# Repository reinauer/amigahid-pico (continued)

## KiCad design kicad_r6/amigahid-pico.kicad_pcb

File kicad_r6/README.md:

# AmigaHID Pico r6 — prototype hardware

Open `amigahid-pico.kicad_pro` with KiCad 10.
The schematic and PCB in this directory are the r6 design, not fabrication-proven hardware.

## Implemented

- Pico **W** (RP2040, LCSC C7203003) fitted by default; also supports Pico **2 W**
  (RP2350) on the same footprint. Both modules provide Wi-Fi/Bluetooth. A bare RP2350 + RM2 design is
  deferred; it requires a separate MCU power/flash/clock/RF layout.
- Two **SN74CBTD3861DBQR** 10-channel bus switches replace all 17 BSS138 level
  shifters. Ten isolated 4 × 10 kΩ resistor arrays replace 34 individual
  pull-ups; unused resistor channels and switch channels are intentionally NC.
  These are the **CBTD** parts, powered from 5 V; CBTLV3861 is not a substitute.
- Two PCB-mounted **female DE9** connectors, numbered by actual DE9 pins rather
  than the old IDC/ribbon interleave. They connect to the Amiga's male ports.
- A **6-pin mini-DIN A4000 keyboard link**, for the user's straight-through
  PS/2-to-PS/2 cable and A4000-to-A3000 mini-DIN/DIN adapter. The signalling is
  Amiga keyboard protocol. This is not a PC PS/2 keyboard input.
- A four-pin female OLED socket, **3V3 / GND / SCL / SDA**, matching the supplied
  SH1106 module pin table. GPIO2 is SDA; GPIO3 is SCL.
- Four 3.2 mm carrier holes for M3 nylon standoffs on **30.50 × 28.60 mm** centres.
  The OLED outline is **35.50 × 33.70 mm**, from the supplied mechanical drawing.
- One USB-A host port. Full underside Pico W USB pads replace the old board
  crevice / half-via attachment. GPIO14/15 are exposed at J8 for a future PIO-USB
  experiment; the USB-A port currently uses the native USB controller.
- External 5 V input and a power-source selector, plus a 500 mA hold PTC on the
  USB host branch. An external powered USB hub provides multiple device ports.

Two additional case mounts, H5 at (2.70, 63.00) mm and H6 at (53.30, 22.50) mm,
use **2.2 mm holes for M2 nylon screws/standoffs**. Coordinates are measured from
the top-left board corner. Use hardware no wider than 4.4 mm at the PCB; M3
hardware crowds the Pico. H1–H4 remain the OLED mounts.

The carrier has a **14 × 9 mm antenna notch** from x=10 to 24 mm and y=59 to
68 mm, open to the bottom edge. This removes the carrier substrate beneath the
antenna, following the module footprint’s suggested board edge. Keep case metal
and mounting hardware out of that antenna space.

Board bounding outline: **70 × 68 mm**, two copper layers. The bounding rectangle is about 6.4% greater area
than the original outline's 61.772 × 72.443 mm bounding box. The level-shifting
section is smaller; the direct connectors and OLED mounting determine the
carrier size. Three onboard USB sockets and an onboard hub are not included.

## LCSC sourcing

`SOURCING.csv` records the selected manufacturer part numbers, datasheet links,
and footprint checks. The schematic
and PCB use only **LCSC Part #**, the field recognized by the Fabrication Toolkit
plugin. `production/bom.csv` uses the same **LCSC Part #** column. LCSC stock does not itself guarantee JLC assembly stock
or eligibility; check those when uploading the BOM.

All 32 electrical components have LCSC selections. **U1 is Pico W,
C7203003**, selected after checking both official pinouts and SMT drawings.
Pico 2 W is an optional separately sourced alternative. Use firmware built for
`pico_w` with the fitted RP2040 module or `pico2_w` with the RP2350 alternative. The OLED, standoffs, cables, and JP1 shunt are separate assembly
accessories; mounting holes are not purchasable components.

- U1: C7203003, Raspberry Pi Pico W. See `review/sourcing/pico-compatibility.txt`
  for the underside-pad and shell-contact verification.
- U2/U3: C44508, TI SN74CBTD3861DBQR (SSOP-24, 0.635 mm pitch). This replaces
  the initially selected PWR/TSSOP package; the electrical pin assignments are
  unchanged. Use the updated PCB, not the previous TSSOP fabrication files.
- J7: C7428703, HOOYA DIN-603. The six signal holes, 13.9 mm shield spacing,
  central 3 × 1 mm shield slot, and signal numbering match the local footprint.
  Numbering was cross-checked against LCSC’s EasyEDA model as well as the drawing.
- J5/J6: C50380980, LCK-205A09FJ2A00B1A. Signal drills are 1.10 mm to meet the
  supplier’s 1.09 mm hole recommendation; 25 mm mounting-hole pitch is retained.
- J4: C7279912, JST UBA-4R-D14-4D(LF)(SN), matching the existing USB signal and
  shield-hole pattern. USB routing is retained.
- Connector 3D bodies are illustrative, not exact supplier mechanical models.

Check component availability before ordering; sourcing records do not guarantee
stock or reserve parts.

Assembly rotation corrections use `FT Rotation Offset` for Fabrication Toolkit:
U1 = 270°, C4 = 180°, J7 = 0°, and J1–J6/J8/J9/JP1 = 90°.
These offsets incorporate the assembly-preview corrections: U1 and C4 turned
180° from the preceding export, and J7 turned 90° clockwise. They affect only
exported placement rotation. Review pin 1, C4 polarity and connector openings
in the JLC preview after re-uploading the CPL.

## Power and assembly

**Default: regulated 5 V into J9, with a 2 mm pitch shunt on JP1 pins 2–3.**
J9 pin 1 is +5 V input; pin 2 is ground. Supply at least the measured Pico +
peripheral load; a current-limited 5 V bench supply is appropriate for bring-up.
The selector keeps the Amiga's keyboard +5 V separate in external-power mode.
Do not bridge both selector positions. Grounds remain common. Power the adapter and Amiga together; automatic I/O
isolation when either supply is off is not implemented and needs bench review.

JP1 pins 1–2 select power from the Amiga keyboard connector. Use that option
only after checking the actual machine's port budget; the complete 500 mA USB
branch must not be assumed available from a keyboard port. The PTC is overload
protection, not a precise 500 mA current regulator or a USB power-distribution
switch. Use a powered hub for multiple USB loads. DE9 pin 7 is deliberately NC
on both ports, so mouse-port supplies are not paralleled with keyboard power.

D1 feeds Pico VSYS through a Schottky diode, preventing the Pico's programming
USB supply from feeding the selected board rail. Disconnect host devices when
connecting a PC to the Pico's native USB connector: the two connectors share
D+/D-. Do not connect two USB hosts to those data lines.

The Pico module must be **surface mounted/reflowed**, including TP2 and TP3;
plugging it into ordinary 40-pin sockets does not connect the USB test pads.
The local Pico footprint retains the wireless antenna keepouts and omits only
two paste-only apertures which conflicted with its RF keepout. No connector,
OLED metalwork, ground fill or trace should extend into the antenna keepout.

The OLED pin row starts 11.28 mm to the right of the upper-left mounting-hole
centre and 1.54 mm below its PCB top edge, following the supplied drawing.
Use a matching four-pin female socket on the carrier. Approximately 11 mm
board-to-board spacing suits an 8.5 mm socket plus a 2.54 mm male-header body;
**dry-fit the actual supplied header and standoffs before assembly**. All four
OLED holes are part of the carrier; the module outline is on Dwgs.User.
Use nylon spacers to avoid shorting OLED tracks. The display sits above the
carrier components; confirm connector insertion clearance in the assembled stack.

## Connector pinouts

| Connector | Pins |
|---|---|
| J1 A500 | 1 KCLK, 2 KDAT, 3 /RESET, 4 Amiga +5 V, 5 NC, 6 GND, 7 NC, 8 NC |
| J2 UART/SWD | 1 GND, 2 GPIO0/TX, 3 GPIO1/RX, 4 SWDIO, 5 GND, 6 SWCLK |
| J3 OLED | 1 3V3, 2 GND, 3 SCL/GPIO3, 4 SDA/GPIO2 |
| J5/J6 DE9 | 1 Up, 2 Down, 3 Left, 4 Right, 5 button 3, 6 Fire, 7 NC, 8 GND, 9 button 2 |
| J7 A4000 | 1 KDAT, 2 NC, 3 GND, 4 Amiga +5 V, 5 KCLK, 6 NC; shell GND |
| J8 experiment | 1 GND, 2 GPIO14, 3 GPIO15, 4 3V3; no USB firmware or 5 V power at this header |
| J9 external supply | 1 regulated +5 V, 2 GND |
| JP1 2 mm selector | 1 Amiga +5 V, 2 board +5 V, 3 external +5 V; fit one shunt, default 2–3 |

Check the PS/2 cable for **pin-for-pin continuity**, especially 1, 3, 4 and 5.
The A3000 adapter must map A4000 mini-DIN data/clock/ground/supply to the matching
A3000 DIN signals. Do not infer numbering from the mating face or wire colours.
The mini-DIN does not carry A500 /RESET; J1 retains that signal.

## Firmware compatibility

Amiga GPIO assignments retain `BOARD_HIDPICO_REV5`, including the corrected
port-2 GPIO26/GPIO27 mapping. Firmware must drive the Amiga outputs LOW or
release them; the existing keyboard and controller drivers already do that.
The bus switches do not actively generate a 5 V HIGH; the 5 V pull-ups do.

Pico 2 W requires a `pico2_w`/RP2350 firmware build with Bluetooth enabled;
Pico W requires `pico_w`/RP2040. A wireless footprint alone does not enable
Bluetooth in a firmware image. Ensure settings and Bluetooth pairing storage
have non-overlapping flash allocations for the selected target.

Build with `-DDISPLAY_CONTROLLER=SH1106` for the SH1106 module. SSD1306 is the
firmware default and uses a different addressing mode. See
[OLED controller selection](../src/display/README.md) for configuration and
module compatibility checks.

Before promoting this prototype to a manufacturing release:

1. Dry-fit the selected connectors, OLED/socket/spacers and cables. Supplier
   footprint checks and the exact selected parts are recorded in `SOURCING.csv`.
2. Check continuity, diode polarity, power selector isolation and all connector
   pinouts without an Amiga attached. Verify 5 V supply and 3.3 V rail sequencing.
3. Scope LOW/HIGH levels on both sides of both CBTD3861s under actual Amiga
   pull-ups and cable loads, including reset, simultaneous transitions, startup
   and shutdown. TI specifies the part's operating supply as 4.5–5.5 V.
4. Check the Pico pins for overshoot/back-powering in every supply state. The
   CBTD3861's transfer curve is not an absolute overvoltage clamp guarantee.
5. Test USB enumeration/hotplug with a keyboard, mouse and joystick through a
   powered hub. Check inrush, PTC heating, supply drop and USB waveform quality.
   The manually routed pair is matched to below 0.3 mm; this alone is not USB
   compliance or a verified 90-ohm impedance calculation for a chosen fab stackup.
6. Verify Bluetooth operation and RF range with the display and enclosure fitted.
7. Verify the SH1106 image reaches all display edges.

## Files and reproducibility

- `amigahid-pico.kicad_pro`, `.kicad_sch`, `.kicad_pcb`: editable r6 project.
- `SOURCING.csv`: reviewed electrical component list with `LCSC Part #` fields.
  Run `python3 scripts/sync_sourcing.py` to generate `BOM.csv`; add OLED, a 2 mm shunt,
  four M3 nylon spacers and mating power/display connectors to the assembly order.
- `review/oled-*.png` and `review/sourcing/`: supplied mechanical drawings and
  sourcing evidence. Downloadable supplier PDFs are linked in `SOURCING.csv`.
  Exported schematics, board previews, validation reports, Gerbers and production
  files are generated locally and excluded from Git.
- `scripts/sync_sourcing.py`: reapplies reviewed `SOURCING.csv` metadata to the
  schematic, PCB and BOMs without changing the circuit or layout. It does not
  refresh live stock automatically.
- `scripts/validate_r6.py`: repeat the connectivity, mechanics, ERC and DRC checks
  using `/usr/bin/python3 scripts/validate_r6.py` from this directory.
- Local footprint/symbol libraries are project-relative. Only the four r6
  footprints and the required mini-DIN model are tracked. KiCad 10 supplies the
  remaining standard footprints and models. r5 references, caches and one-off
  placement/routing generators are excluded from Git.

## Sources

- [TI SN74CBTD3861 product page](https://www.ti.com/product/SN74CBTD3861)
  and [datasheet](https://www.ti.com/lit/ds/symlink/sn74cbtd3861.pdf).
- [Raspberry Pi Pico 2 W datasheet](https://datasheets.raspberrypi.com/picow/pico-2-w-datasheet.pdf).
- [Raspberry Pi RM2 documentation](https://www.raspberrypi.com/documentation/microcontrollers/radio-modules.html).
- [Commodore A4000 schematic, CN175](https://www.amigawiki.org/dnl/schematics/A4000_Rb.pdf).
- [Sino Wealth SH1106 datasheet](https://www.crystalfontz.com/controllers/SinoWealth/SH1106/468/).
- OLED dimensional drawing and pin table under `review/`.

Original project author: nine <nine@aphlor.org>. See the repository README for
the project's Eclipse Public License 2.0 licensing statement.

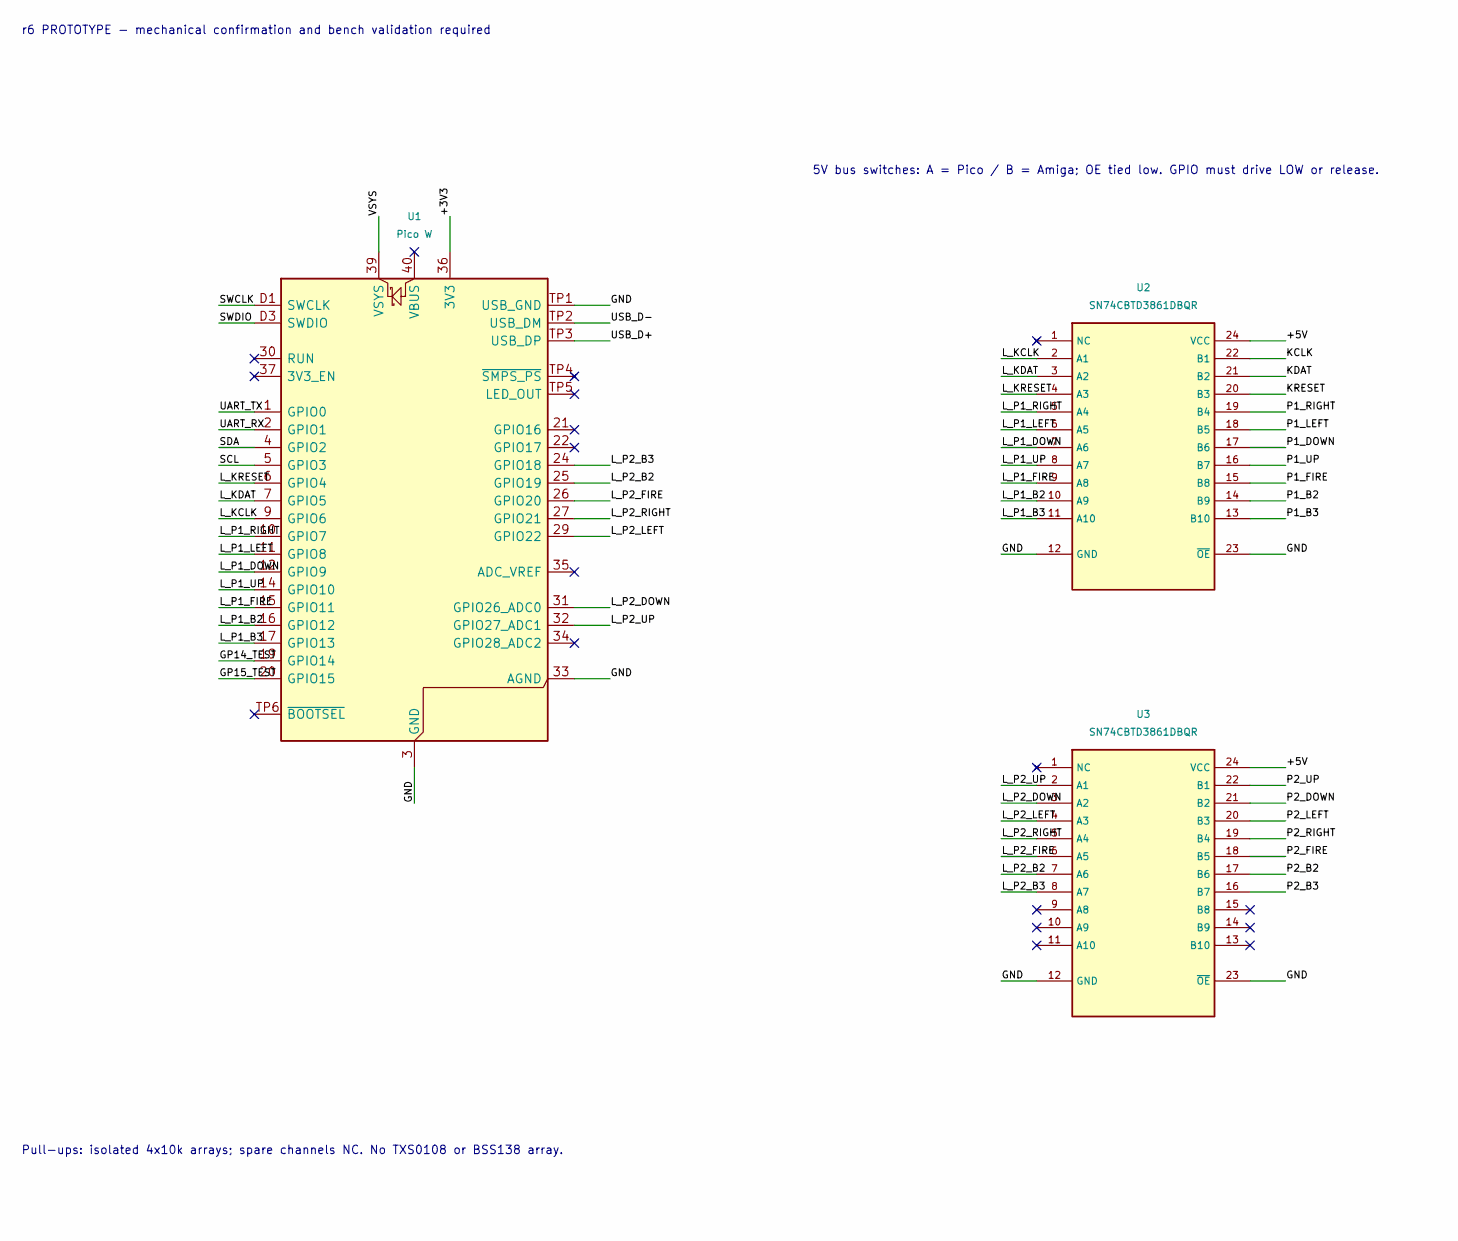
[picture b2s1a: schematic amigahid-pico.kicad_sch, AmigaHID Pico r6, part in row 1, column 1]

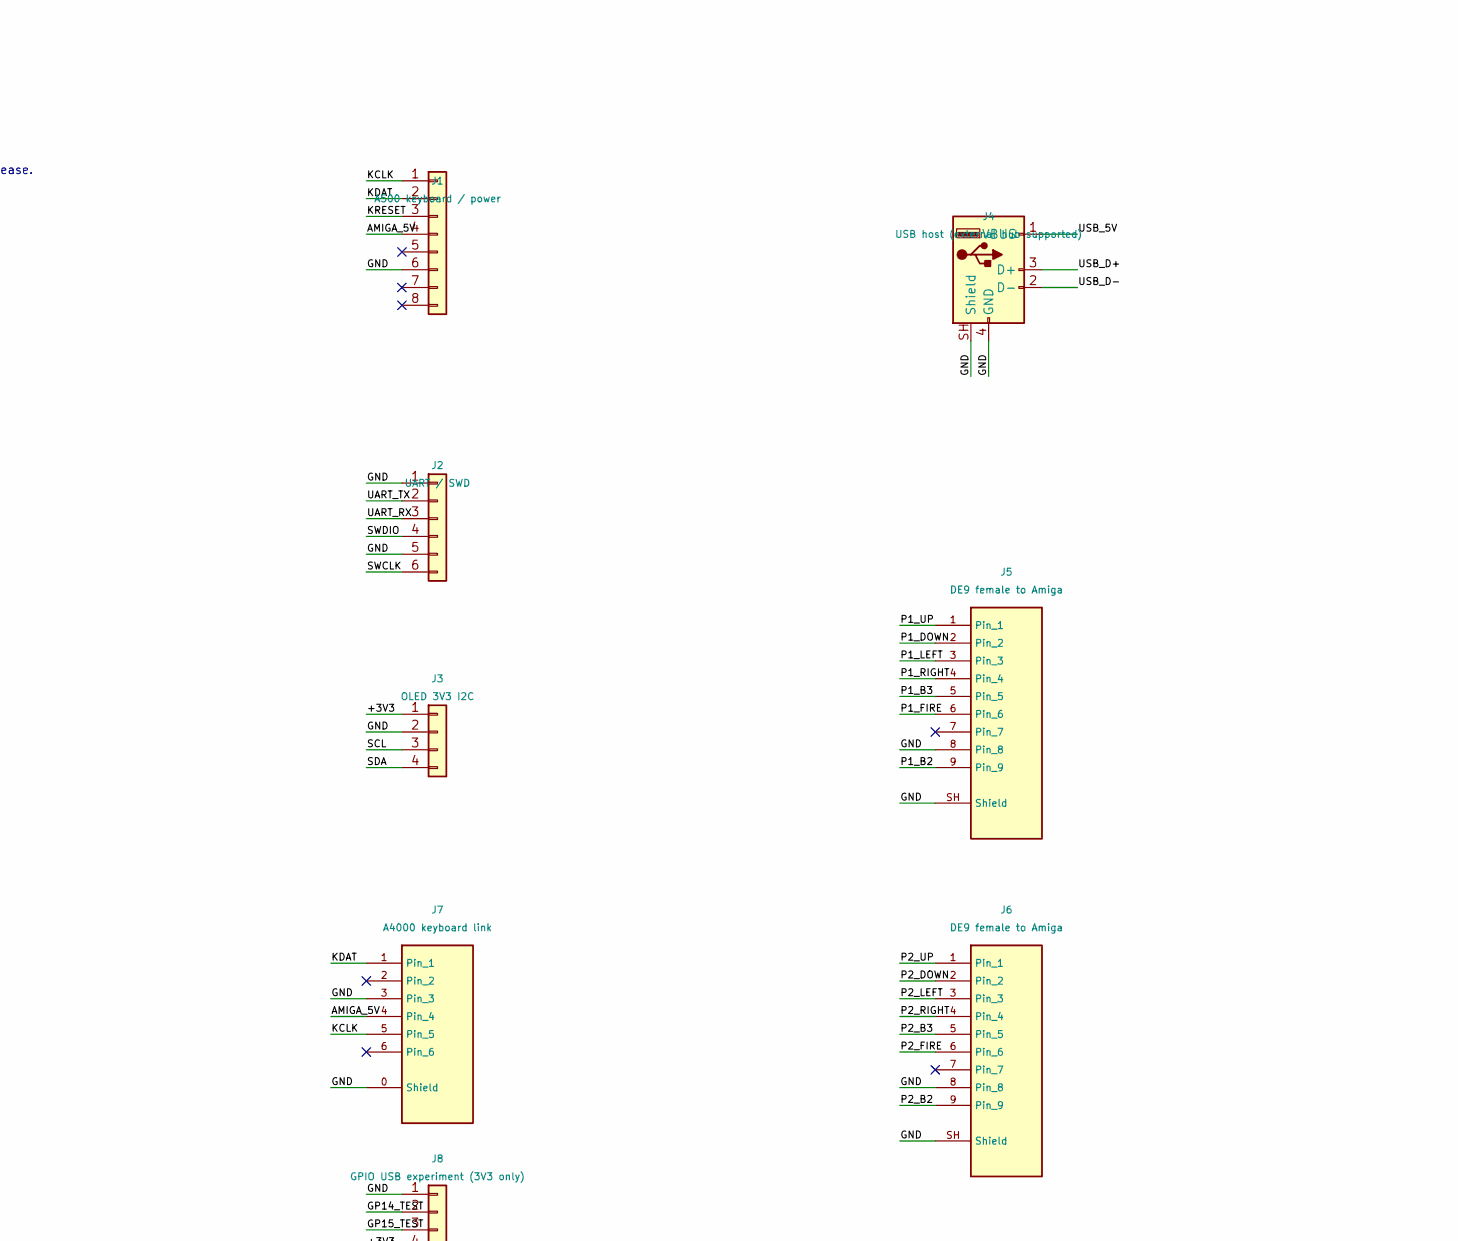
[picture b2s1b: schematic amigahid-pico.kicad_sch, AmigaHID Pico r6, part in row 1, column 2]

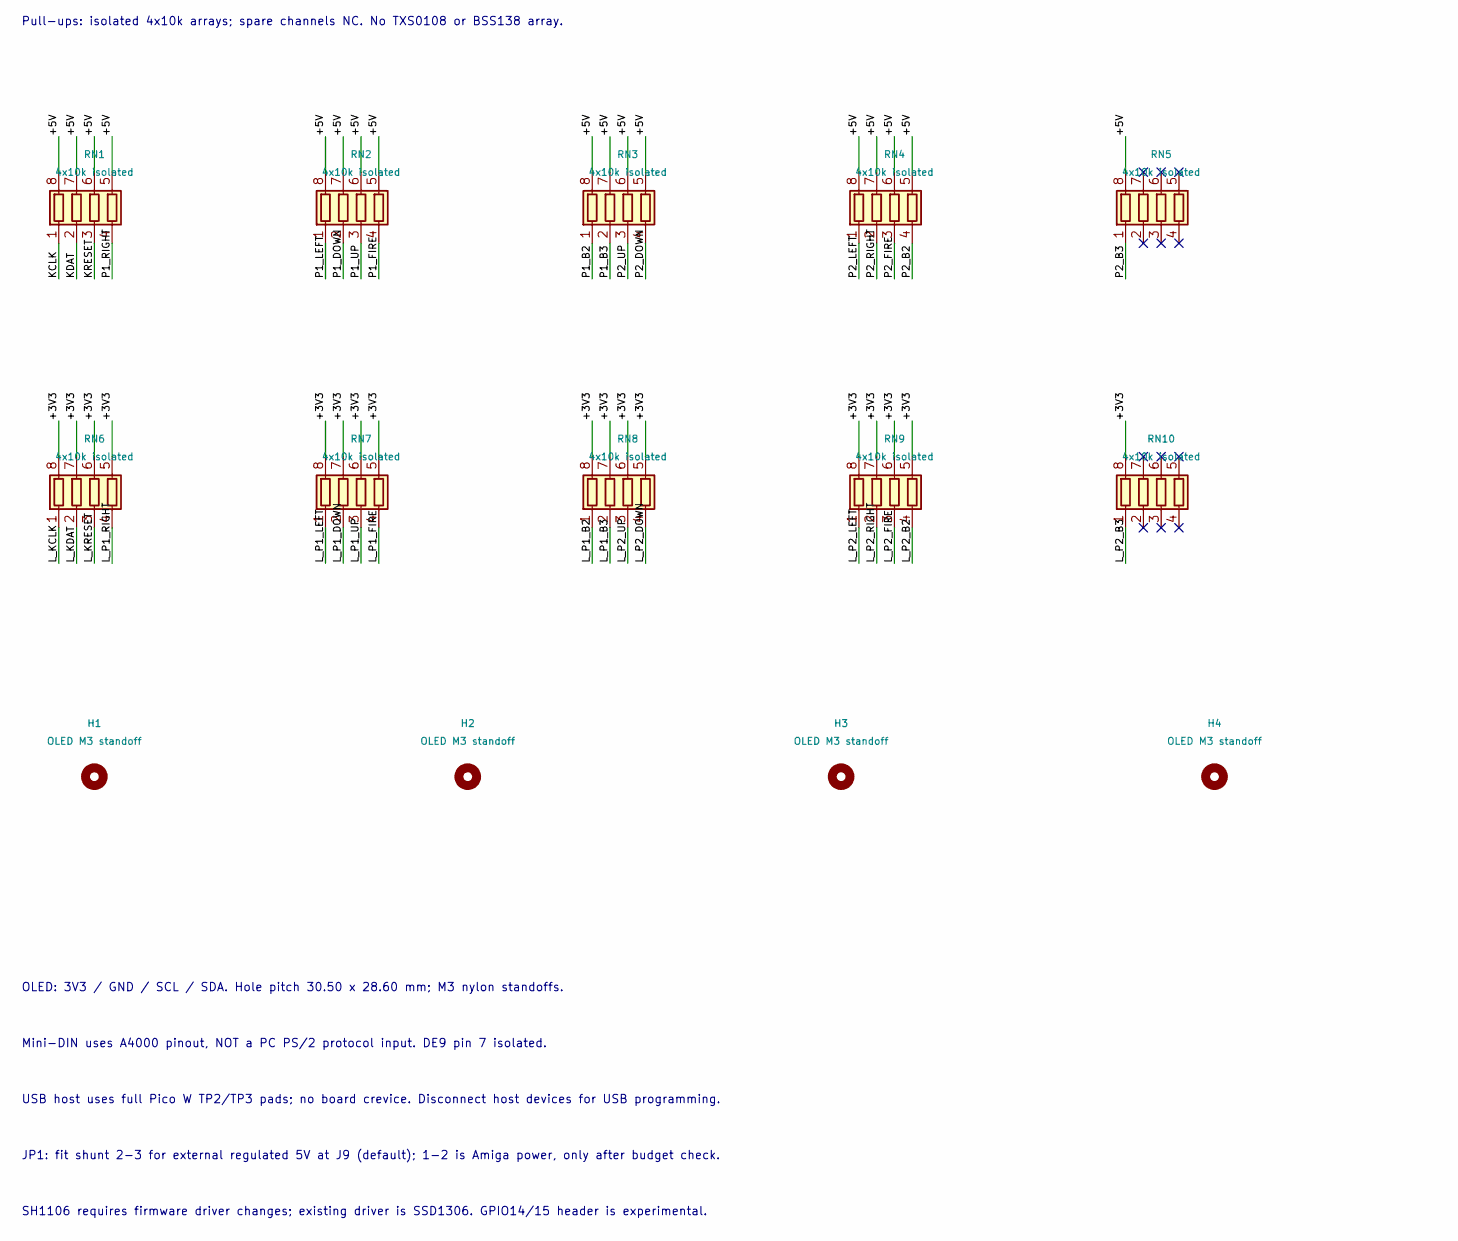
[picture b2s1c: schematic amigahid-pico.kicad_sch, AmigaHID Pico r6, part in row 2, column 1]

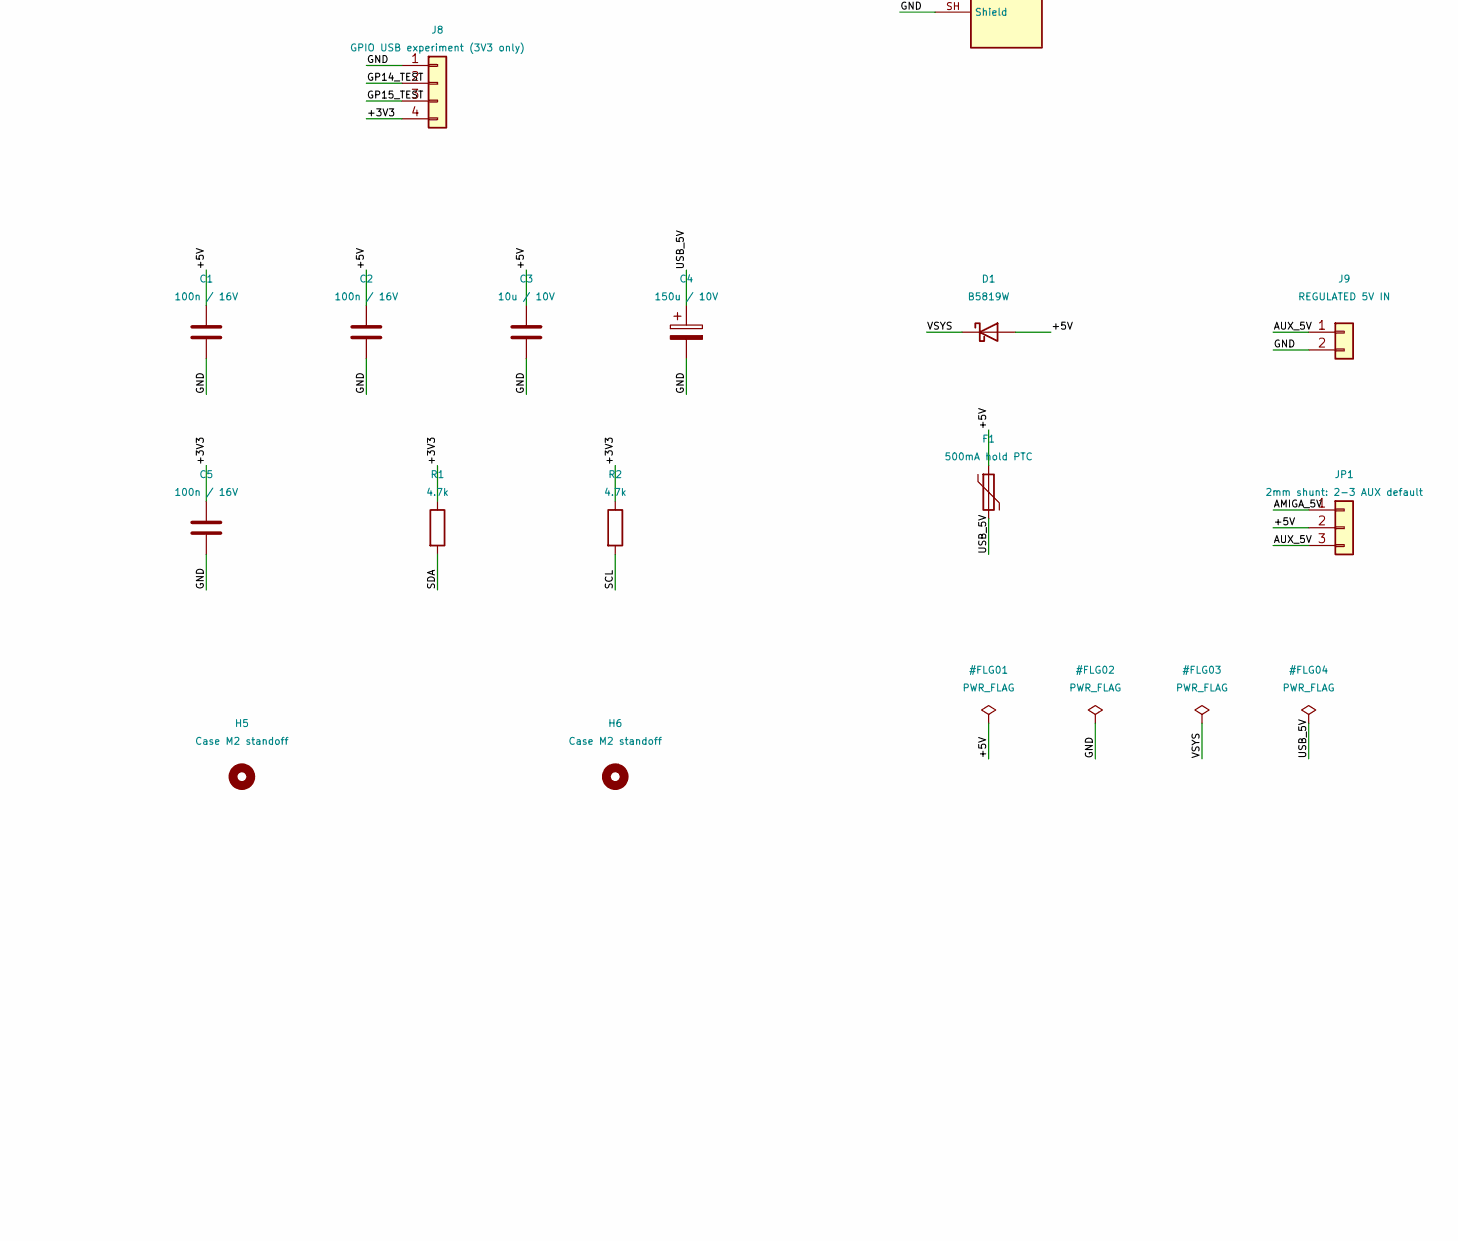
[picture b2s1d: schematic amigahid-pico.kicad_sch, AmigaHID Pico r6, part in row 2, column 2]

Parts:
C1, C2, C5: 100n / 16V; C_0603_1608Metric; MPN CC0603KRX7R9BB104; LCSC Stock 8519800
C3: 10u / 10V; C_0805_2012Metric; MPN CL21A106KAYNNNE; LCSC Stock 594040
C4: 150u / 10V; CP_Elec_6.3x5.4; MPN RVT1A151M0605 150UF 10V; LCSC Stock 520
D1: B5819W; D_SOD-123; MPN B5819W SL; LCSC Stock 229920
F1: 500mA hold PTC; Fuse_1206_3216Metric; MPN MF-NSMF050-2; LCSC Stock 59460
H1, H2, H3, H4: OLED M3 standoff; MountingHole_3.2mm_M3
H5, H6: Case M2 standoff; MountingHole_2.2mm_M2
J1: A500 keyboard / power; PinHeader_1x08_P2.54mm_Vertical; MPN X6511WV-08H-C60D30; LCSC Stock 610
J2: UART / SWD; PinHeader_1x06_P2.54mm_Vertical; MPN X6511WV-06H-C60D30; LCSC Stock 400
J3: OLED 3V3 I2C; PinSocket_1x04_P2.54mm_Vertical; MPN DS1023-1x4SF11; LCSC Stock 2530
J4: USB host (external hub supported); USB_A_R6; MPN UBA-4R-D14-4D(LF)(SN); LCSC Stock 265
J5, J6: DE9 female to Amiga; DE9_Female_R6; MPN LCK-205A09FJ2A00B1A; LCSC Stock 1935
J7: A4000 keyboard link; MiniDIN6_R6; MPN DIN-603; LCSC Stock 225
J8: GPIO USB experiment (3V3 only); PinHeader_1x04_P2.54mm_Vertical; MPN X6511WV-04H-C60D30; LCSC Stock 26130
J9: REGULATED 5V IN; PinHeader_1x02_P2.54mm_Vertical; MPN X6511WV-02H-C60D30; LCSC Stock 17940
JP1: 2mm shunt: 2-3 AUX default; PinHeader_1x03_P2.00mm_Vertical; MPN PZ2.0-1x3PZZ-L8.7; LCSC Stock 3850
R1, R2: 4.7k; R_0603_1608Metric; MPN 0603WAF4701T5E; LCSC Stock 13626200
RN1, RN2, RN3, RN4, RN5, RN6, RN7, RN8, RN9, RN10: 4x10k isolated; R_Array_Convex_4x0603; MPN EXB38V103JV; LCSC Stock 53500
U1: Pico W; Pico_2_W_R6; MPN Raspberry Pi Pico W; LCSC Stock 855
U2, U3: SN74CBTD3861DBQR; SSOP-24_3.9x8.7mm_P0.635mm; MPN SN74CBTD3861DBQR; LCSC Stock 117

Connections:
/+3V3: C5.1, J3.1, J8.4, R1.1, R2.1, RN6.5 (R4.2), RN6.6 (R3.2), RN6.7 (R2.2), RN6.8 (R1.2), RN7.5 (R4.2), RN7.6 (R3.2), RN7.7 (R2.2), RN7.8 (R1.2), RN8.5 (R4.2), RN8.6 (R3.2), RN8.7 (R2.2), RN8.8 (R1.2), RN9.5 (R4.2), RN9.6 (R3.2), RN9.7 (R2.2), RN9.8 (R1.2), RN10.8 (R1.2), U1.36 (3V3)
/+5V: C1.1, C2.1, C3.1, D1.2 (A), F1.1, JP1.2, RN1.5 (R4.2), RN1.6 (R3.2), RN1.7 (R2.2), RN1.8 (R1.2), RN2.5 (R4.2), RN2.6 (R3.2), RN2.7 (R2.2), RN2.8 (R1.2), RN3.5 (R4.2), RN3.6 (R3.2), RN3.7 (R2.2), RN3.8 (R1.2), RN4.5 (R4.2), RN4.6 (R3.2), RN4.7 (R2.2), RN4.8 (R1.2), RN5.8 (R1.2), U2.24 (VCC), U3.24 (VCC)
/AMIGA_5V: J1.4, J7.4, JP1.1
/AUX_5V: J9.1, JP1.3
/GP14_TEST: J8.2, U1.19 (GPIO14)
/GP15_TEST: J8.3, U1.20 (GPIO15)
/KCLK: J1.1, J7.5, RN1.1 (R1.1), U2.22 (B1)
/KDAT: J1.2, J7.1, RN1.2 (R2.1), U2.21 (B2)
/KRESET: J1.3, RN1.3 (R3.1), U2.20 (B3)
/L_KCLK: RN6.1 (R1.1), U1.9 (GPIO6), U2.2 (A1)
/L_KDAT: RN6.2 (R2.1), U1.7 (GPIO5), U2.3 (A2)
/L_KRESET: RN6.3 (R3.1), U1.6 (GPIO4), U2.4 (A3)
/L_P1_B2: RN8.1 (R1.1), U1.16 (GPIO12), U2.10 (A9)
/L_P1_B3: RN8.2 (R2.1), U1.17 (GPIO13), U2.11 (A10)
/L_P1_DOWN: RN7.2 (R2.1), U1.12 (GPIO9), U2.7 (A6)
/L_P1_FIRE: RN7.4 (R4.1), U1.15 (GPIO11), U2.9 (A8)
/L_P1_LEFT: RN7.1 (R1.1), U1.11 (GPIO8), U2.6 (A5)
/L_P1_RIGHT: RN6.4 (R4.1), U1.10 (GPIO7), U2.5 (A4)
/L_P1_UP: RN7.3 (R3.1), U1.14 (GPIO10), U2.8 (A7)
/L_P2_B2: RN9.4 (R4.1), U1.25 (GPIO19), U3.7 (A6)
/L_P2_B3: RN10.1 (R1.1), U1.24 (GPIO18), U3.8 (A7)
/L_P2_DOWN: RN8.4 (R4.1), U1.31 (GPIO26_ADC0), U3.3 (A2)
/L_P2_FIRE: RN9.3 (R3.1), U1.26 (GPIO20), U3.6 (A5)
/L_P2_LEFT: RN9.1 (R1.1), U1.29 (GPIO22), U3.4 (A3)
/L_P2_RIGHT: RN9.2 (R2.1), U1.27 (GPIO21), U3.5 (A4)
/L_P2_UP: RN8.3 (R3.1), U1.32 (GPIO27_ADC1), U3.2 (A1)
/P1_B2: J5.9, RN3.1 (R1.1), U2.14 (B9)
/P1_B3: J5.5, RN3.2 (R2.1), U2.13 (B10)
/P1_DOWN: J5.2, RN2.2 (R2.1), U2.17 (B6)
/P1_FIRE: J5.6, RN2.4 (R4.1), U2.15 (B8)
/P1_LEFT: J5.3, RN2.1 (R1.1), U2.18 (B5)
/P1_RIGHT: J5.4, RN1.4 (R4.1), U2.19 (B4)
/P1_UP: J5.1, RN2.3 (R3.1), U2.16 (B7)
/P2_B2: J6.9, RN4.4 (R4.1), U3.17 (B6)
/P2_B3: J6.5, RN5.1 (R1.1), U3.16 (B7)
/P2_DOWN: J6.2, RN3.4 (R4.1), U3.21 (B2)
/P2_FIRE: J6.6, RN4.3 (R3.1), U3.18 (B5)
/P2_LEFT: J6.3, RN4.1 (R1.1), U3.20 (B3)
/P2_RIGHT: J6.4, RN4.2 (R2.1), U3.19 (B4)
/P2_UP: J6.1, RN3.3 (R3.1), U3.22 (B1)
/SCL: J3.3, R2.2, U1.5 (GPIO3)
/SDA: J3.4, R1.2, U1.4 (GPIO2)
/SWCLK: J2.6, U1.D1 (SWCLK)
/SWDIO: J2.4, U1.D3 (SWDIO)
/UART_RX: J2.3, U1.2 (GPIO1)
/UART_TX: J2.2, U1.1 (GPIO0)
/USB_5V: C4.1, F1.2, J4.1 (VBUS)
/USB_D+: J4.3 (D+), U1.TP3 (USB_DP)
/USB_D-: J4.2 (D-), U1.TP2 (USB_DM)
/VSYS: D1.1 (K), U1.39 (VSYS)
GND: C1.2, C2.2, C3.2, C4.2, C5.2, J1.6, J2.1, J2.5, J3.2, J4.4 (GND), J4.SH (Shield), J5.8, J5.SH (Shield), J6.8, J6.SH (Shield), J7.0 (Shield), J7.3, J8.1, J9.2, U1.3 (GND), U1.8 (GND), U1.13 (GND), U1.18 (GND), U1.23 (GND), U1.28 (GND), U1.33 (AGND), U1.38 (GND), U1.D2 (GND), U1.TP1 (USB_GND), U2.12 (GND), U2.23 (~OE), U3.12 (GND), U3.23 (~OE)

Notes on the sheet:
r6 PROTOTYPE - mechanical confirmation and bench validation required
5V bus switches: A = Pico / B = Amiga; OE tied low. GPIO must drive LOW or release.
Pull-ups: isolated 4x10k arrays; spare channels NC. No TXS0108 or BSS138 array.
OLED: 3V3 / GND / SCL / SDA. Hole pitch 30.50 x 28.60 mm; M3 nylon standoffs.
Mini-DIN uses A4000 pinout, NOT a PC PS/2 protocol input. DE9 pin 7 isolated.
USB host uses full Pico W TP2/TP3 pads; no board crevice. Disconnect host devices for USB programming.
JP1: fit shunt 2-3 for external regulated 5V at J9 (default); 1-2 is Amiga power, only after budget check.
SH1106 requires firmware driver changes; existing driver is SSD1306. GPIO14/15 header is experimental.

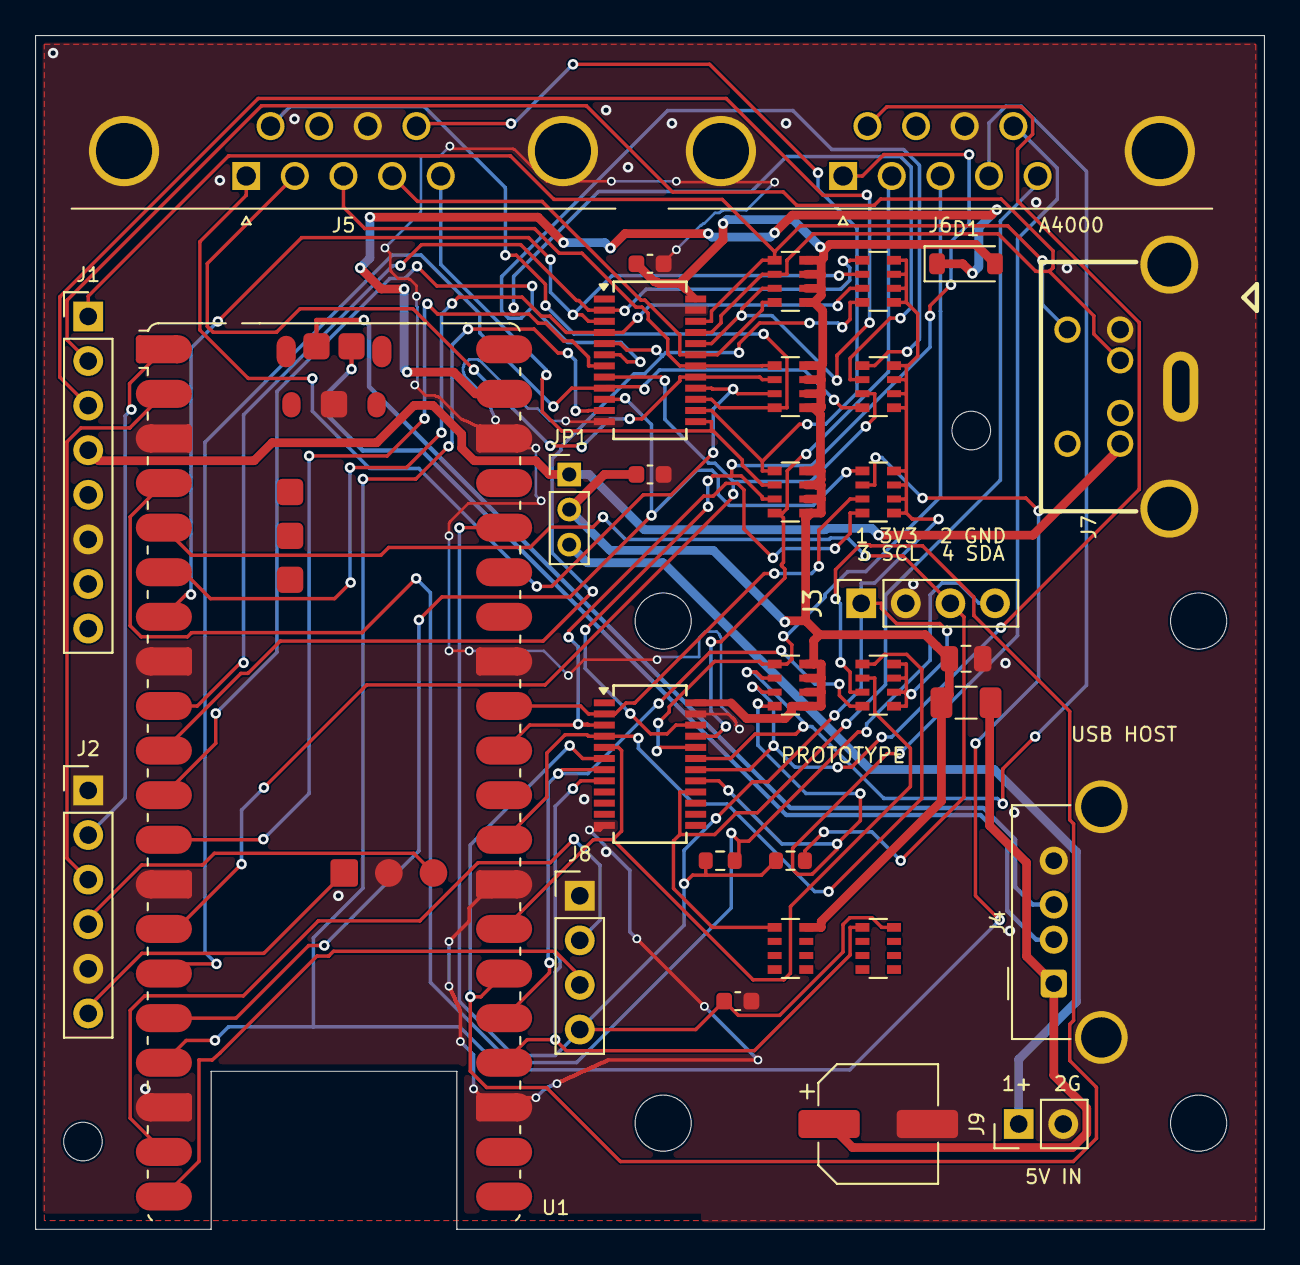
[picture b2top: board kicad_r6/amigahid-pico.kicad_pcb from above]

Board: 2 copper layers, 70.0 x 68.0 mm, 38 parts (0 on the bottom side), 51 nets.

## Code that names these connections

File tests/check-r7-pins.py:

#!/usr/bin/env python3
"""Compare the compiled REV7 pin map with the hardware source of truth."""
# SPDX-License-Identifier: EPL-2.0
import json
import os
import re
import subprocess
import sys
from pathlib import Path

root = Path(__file__).resolve().parents[1]
sys.path.insert(0, str(root / 'kicad_r7/scripts'))
from sexpr import parse, children, get

parts = {c['ref']: c for c in json.loads((root / 'kicad_r7/circuit.json').read_text())['parts']}
symbols = children(parse((root / 'kicad_r7/r7.kicad_sym').read_text()), 'symbol')
chip = next(s for s in symbols if s[1] == parts['U1']['symbol'])
pins = {}
for unit in children(chip, 'symbol'):
    for pin in children(unit, 'pin'):
        match = re.match(r'GPIO(\d+)', get(pin, 'name')[1])
        if match:
            pins[int(match[1])] = parts['U1']['nets'].get(get(pin, 'number')[1])
# Read the actual SDK board header as well as the application's pin map.
text = subprocess.check_output([
    os.environ.get('CC', 'cc'), '-E', '-dM', '-x', 'c', '-DPICO_RP2350=1',
    '-DBOARD_HIDPICO_REV7', '-I' + str(root / 'tests/stubs'),
    '-I' + str(root / 'pico-sdk/src/boards/include'),
    '-include', str(root / 'cmake/boards/amigahid_r7.h'),
    '-include', str(root / 'src/config.h'), '-'], input='', text=True)
macros = dict(re.findall(r'^#define (\w+)\s+(.*)$', text, re.M))
expected = {
    'PICO_DEFAULT_UART_TX_PIN': 'UART_TX', 'PICO_DEFAULT_UART_RX_PIN': 'UART_RX',
    'I2C_PIN_SDA': 'SDA', 'I2C_PIN_SCL': 'SCL',
    'KBD_AMIGA_DAT': 'L_KDAT', 'KBD_AMIGA_CLK': 'L_KCLK',
    'MENU_LEVER_PIN_LEFT': 'MENU_LEFT_N', 'MENU_LEVER_PIN_RIGHT': 'MENU_RIGHT_N',
    'MENU_LEVER_PIN_PUSH': 'MENU_PUSH_N',
    'CYW43_DEFAULT_PIN_WL_REG_ON': 'WL_ON', 'CYW43_DEFAULT_PIN_WL_CLOCK': 'WL_CLK',
    'CYW43_DEFAULT_PIN_WL_CS': 'WL_CS', 'CYW43_DEFAULT_PIN_WL_DATA_IN': 'WL_DATA',
    'CYW43_DEFAULT_PIN_WL_DATA_OUT': 'WL_DATA', 'CYW43_DEFAULT_PIN_WL_HOST_WAKE': 'WL_DATA',
}
for port in (1, 2):
    for suffix, net in [('HQ', 'RIGHT'), ('VQ', 'LEFT'), ('H', 'DOWN'), ('V', 'UP'),
                        ('B1', 'FIRE'), ('B2', 'B2'), ('B3', 'B3')]:
        expected[f'QM{port}_AMIGA_{suffix}'] = f'L_P{port}_{net}'
for macro, net in expected.items():
    gpio = int(macros[macro].rstrip('uU'))
    assert pins[gpio] == net, (macro, gpio, pins[gpio], net)
assert pins[int(macros['KBD_AMIGA_RST'])] is None
for pin, macro in [('1', 'MENU_LEVER_PIN_LEFT'), ('2', 'MENU_LEVER_PIN_RIGHT'),
                   ('T', 'MENU_LEVER_PIN_PUSH')]:
    assert parts['SW2']['nets'][pin] == expected[macro]
assert macros['PICO_DEFAULT_I2C'] == '1'
assert macros['PICO_DEFAULT_I2C_SDA_PIN'] == macros['I2C_PIN_SDA']
assert macros['PICO_DEFAULT_I2C_SCL_PIN'] == macros['I2C_PIN_SCL']
for unused in ['PICO_VSYS_PIN', 'PICO_DEFAULT_SPI', 'CYW43_WL_GPIO_SMPS_PIN', 'CYW43_WL_GPIO_VBUS_PIN']:
    assert unused not in macros, unused
print('r7 firmware pin map matches circuit.json and the MCU symbol: PASS')

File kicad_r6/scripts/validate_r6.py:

#!/usr/bin/python3
"""Validate r6 connectivity, mechanics, USB matching, ERC and schematic/PCB parity.
Run with system Python (KiCad pcbnew), from any directory. Writes only review reports.
"""
from pathlib import Path
import subprocess,xml.etree.ElementTree as E,json,math,csv,re
import pcbnew as p
R=Path(__file__).resolve().parents[1];review=R/'review';sch=R/'amigahid-pico.kicad_sch';board=R/'amigahid-pico.kicad_pcb'
def run(*args):subprocess.run(['kicad-cli',*map(str,args)],check=True,cwd=R)
run('sch','export','netlist','--format','kicadxml','-o',review/'netlist.xml',sch)
run('sch','erc','--exit-code-violations','--format','json','-o',review/'erc.json',sch)
run('pcb','drc','--schematic-parity','--exit-code-violations','--format','json','-o',review/'drc.json',board)
r=E.parse(review/'netlist.xml').getroot();b=p.LoadBoard(str(board));fps={f.GetReference():f for f in b.GetFootprints()};nets={}
for net in r.find('nets'):
 for node in net:
  ref,pin=node.attrib['ref'],node.attrib['pin'];nets[ref,pin]=net.attrib['name']
  if ref.startswith('#'):continue
  pads=[v for v in fps[ref].Pads() if v.GetNumber()==pin];assert pads,(ref,pin)
  assert all(v.GetNetname()==net.attrib['name'] for v in pads),(ref,pin)
def expect(ref,pin,net):assert nets[ref,str(pin)]==('GND' if net=='GND' else '/'+net),(ref,pin,net,nets[ref,str(pin)])
def nc(ref,pin):assert nets[ref,str(pin)].startswith('unconnected-'),(ref,pin)
# Pin table checked against TI SCDS084G, not inferred from part-number similarity.
high=['KCLK','KDAT','KRESET','P1_RIGHT','P1_LEFT','P1_DOWN','P1_UP','P1_FIRE','P1_B2','P1_B3','P2_UP','P2_DOWN','P2_LEFT','P2_RIGHT','P2_FIRE','P2_B2','P2_B3']
physical=[9,7,6,10,11,12,14,15,16,17,32,31,29,27,26,25,24]
for i,(name,pin) in enumerate(zip(high,physical)):
 ref='U2' if i<10 else 'U3';j=i if i<10 else i-10
 expect('U1',pin,'L_'+name);expect(ref,j+2,'L_'+name);expect(ref,22-j,name)
for ref in ['U2','U3']:
 expect(ref,24,'+5V');expect(ref,12,'GND');expect(ref,23,'GND');nc(ref,1)
for port in [1,2]:
 for pin,suffix in {1:'UP',2:'DOWN',3:'LEFT',4:'RIGHT',5:'B3',6:'FIRE',9:'B2'}.items():expect('J'+str(port+4),pin,f'P{port}_{suffix}')
 expect('J'+str(port+4),8,'GND');nc('J'+str(port+4),7)
for pin,name in {1:'KDAT',3:'GND',4:'AMIGA_5V',5:'KCLK'}.items():expect('J7',pin,name)
for pin in [2,6]:nc('J7',pin)
for pin,name in {1:'+3V3',2:'GND',3:'SCL',4:'SDA'}.items():expect('J3',pin,name)
for ref,pin,name in [('J9',1,'AUX_5V'),('J9',2,'GND'),('JP1',1,'AMIGA_5V'),('JP1',2,'+5V'),('JP1',3,'AUX_5V'),('D1',1,'VSYS'),('D1',2,'+5V'),('F1',1,'+5V'),('F1',2,'USB_5V'),('J4',1,'USB_5V'),('U1','TP2','USB_D-'),('U1','TP3','USB_D+')]:expect(ref,pin,name)
assert len({nets['JP1',str(i)] for i in [1,2,3]})==3,'Power sources must not be shorted on copper'
assert not any(f.GetValue() in ['BSS138','TXS0108','TXS0108E'] for f in fps.values())
positions={ref:(f.GetPosition().x/1e6,f.GetPosition().y/1e6) for ref,f in fps.items()}
x,y=positions['H1'];assert positions['H2']==(x+30.5,y);assert positions['H3']==(x,round(y+28.6,2));assert positions['H4']==(x+30.5,round(y+28.6,2))
assert 'PinSocket' in str(fps['J3'].GetFPID().GetLibItemName())
lengths={n:sum(t.GetLength() for t in b.GetTracks() if t.GetNetname()=='/'+n and not isinstance(t,p.PCB_VIA))/1e6 for n in ['USB_D+','USB_D-']}
assert abs(lengths['USB_D+']-lengths['USB_D-'])<.3,lengths
report=json.loads((review/'drc.json').read_text());assert not any(report[k] for k in ['violations','unconnected_items','schematic_parity'])
project=json.loads((R/'amigahid-pico.kicad_pro').read_text());assert not project['board']['design_settings']['drc_exclusions']
# Verify procurement fields against the reviewed stock snapshot and fitted packages.
source={row['Reference']:row for row in csv.DictReader((R/'SOURCING.csv').open())}
snapshot=json.loads((review/'sourcing/stock-snapshot.json').read_text())
from sexpr import parse,children
schematic_props={}
for symbol in children(parse(sch.read_text()),'symbol'):
 props={v[1]:v[2] for v in children(symbol,'property')}
 schematic_props[props['Reference']]=props
for ref,row in source.items():
 code=row['LCSC Part #']
 assert schematic_props[ref]['LCSC Part #']==code
 assert fps[ref].GetField('LCSC Part #').GetText()==code
 assert not fps[ref].HasField('LCSC #')
 assert 'LCSC #' not in schematic_props[ref]
 assert fps[ref].GetField('MPN').GetText()==row['MPN']
 if code:
  assert re.fullmatch(r'C[0-9]+',code)
  assert snapshot[code]['stock']>0 and snapshot[code]['ships_immediately']>0
  assert snapshot[code]['mpn']==row['MPN']
  assert str(snapshot[code]['stock'])==row['Stock at check']
 else:
  raise AssertionError(('Missing stocked selection', ref))
for ref in ['U2','U3']:
 assert fps[ref].GetValue()=='SN74CBTD3861DBQR'
 assert str(fps[ref].GetFPID().GetLibItemName())=='SSOP-24_3.9x8.7mm_P0.635mm'
 pads={v.GetNumber():v for v in fps[ref].Pads()}
 assert abs(pads['2'].GetPosition().y-pads['1'].GetPosition().y)==p.FromMM(.635)
for ref in ['J5','J6']:
 for pad in fps[ref].Pads():
  if pad.GetNumber().isdigit():assert pad.GetDrillSize().x==p.FromMM(1.1)
result={'status':'PASS','stocked_lcsc_components':32,'separately_sourced':[],'kicad':p.Version(),'pcb_components':len(fps),'checked_schematic_pin_assignments':sum(not ref.startswith('#') for ref,pin in nets),'level_shift_channels':17,'usb_trace_lengths_mm':lengths,'usb_skew_mm':abs(lengths['USB_D+']-lengths['USB_D-']),'oled_hole_pitch_mm':[30.5,28.6],'drc_violations':0,'unconnected':0,'schematic_parity_issues':0,'erc_violations':0,'bench_validation':'NOT PERFORMED','firmware':'Pico 2 W Bluetooth build blocked by existing flash-storage overlap; SH1106 driver not implemented'}
(review/'validation.json').write_text(json.dumps(result,indent=2)+'\n');print(json.dumps(result,indent=2))

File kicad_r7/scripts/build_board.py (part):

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reference=R/'reference/RP2350A-minimal.kicad_pcb'
if reference.exists():
    source=p.LoadBoard(str(reference))
    mapping={'+3V3':'+3V3','+1V1':'+1V1','GND':'GND','/VREG_LX':'VREG_LX','/VREG_AVDD':'VREG_AVDD','/XIN':'XIN','/XOUT':'XOUT',
             'Net-(X1-3)':'XTAL_OUT','Net-(U1-USB_DM)':'USB_DM_MCU','Net-(U1-USB_DP)':'USB_DP_MCU'}
    for t in source.GetTracks():
        target=mapping.get(t.GetNetname())
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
